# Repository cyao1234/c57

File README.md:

# c57

Low-cost bluetooth devboard with a ch572 MCU. To program it press the boot button, and use either mountriver studio or [ch32fun](https://github.com/cnlohr/ch32fun).

It is also very-low powered, and has on-board USB-C connector.

Features:
- Low-cost wch antenna
- On board antenna 
- Bootloader via USB
- Bare metal
- A lot of gpio
- on board usb c

This devboard lets you do low cost and low powered bluetooth communications. Best used with ch32fun

| Item | Price | Where |
| ---- | ----- | ----- |
| PCB + PCBA | $50 | JLC |

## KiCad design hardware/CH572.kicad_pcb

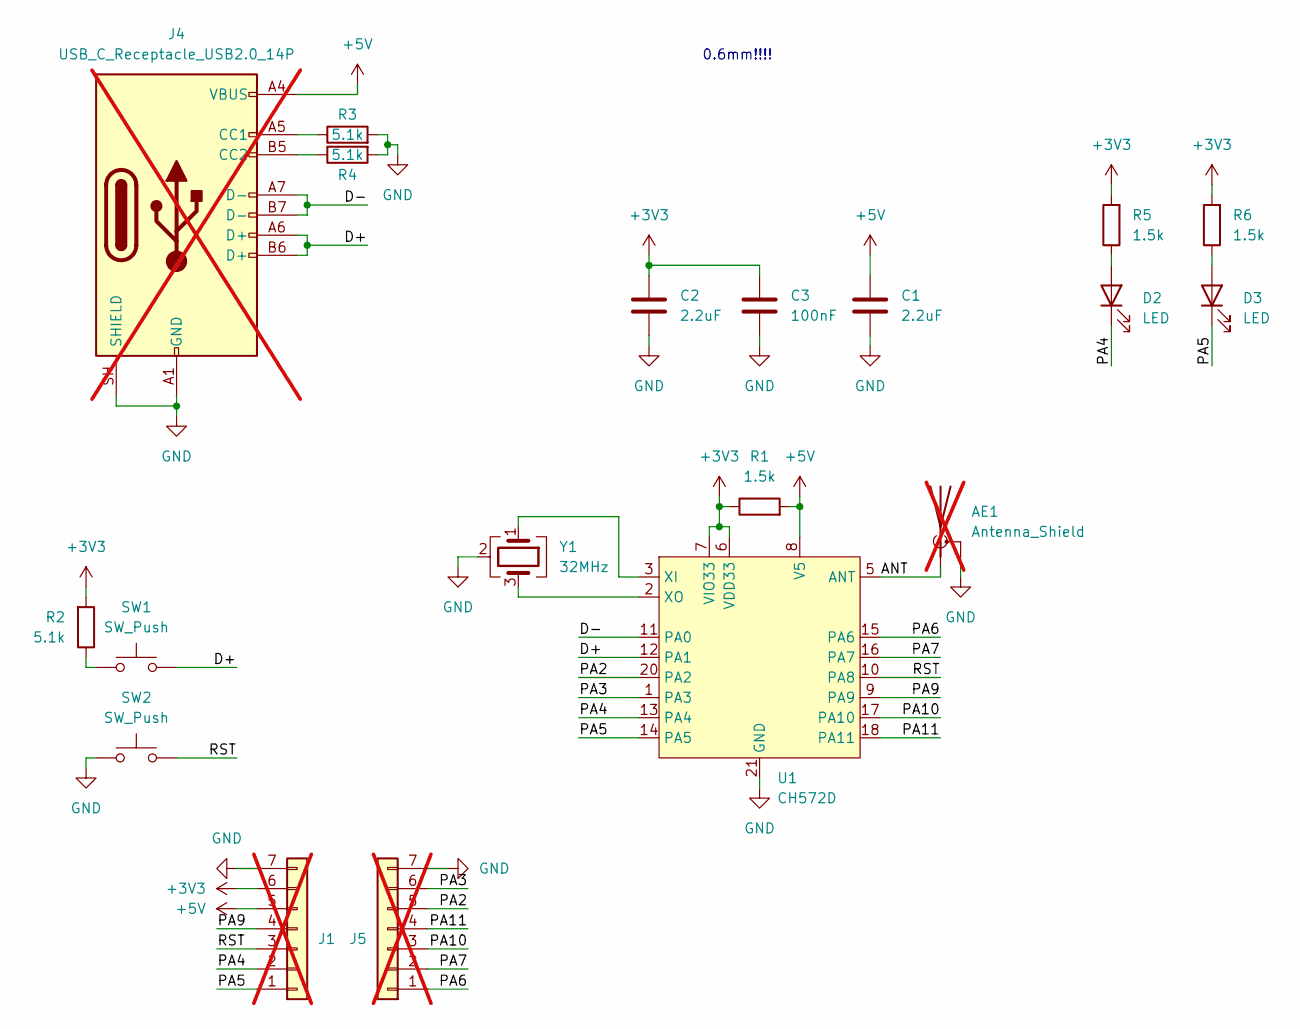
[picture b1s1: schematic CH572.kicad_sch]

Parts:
AE1: Antenna_Shield; WCH_CH572_2.4GHz; not fitted
C1, C2: 2.2uF; C_0402_1005Metric; LCSC Part # C159814
C3: 100nF; C_0402_1005Metric; LCSC Part # C466234
D2, D3: LED; LED_0402_1005Metric; LCSC Part # C965793
J1, J5: Conn_01x07; Castellated_1x07_P2.54mm_Vertical; not fitted
J4: USB_C_Receptacle_USB2.0_14P; USB_C_PADDLE; not fitted
R1, R5, R6: 1.5k; R_0402_1005Metric; LCSC Part # C25867
R2, R3, R4: 5.1k; R_0402_1005Metric; LCSC Part # C2906874
SW1, SW2: SW_Push; SW_Push_SPST_TSA016; LCSC Part # C2888428
U1: CH572D; UQFN-20-1EP_3x3mm_P0.4mm_EP1.85x1.85mm_ThermalVias; LCSC Part # C46597863
Y1: 32MHz; Crystal_SMD_2016-4Pin_2.0x1.6mm; LCSC Part # C2965584

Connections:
+3V3: C2.1, C3.1, J1.6, R1.1, R2.2, R5.2, R6.2, U1.6 (VDD33), U1.7 (VIO33)
+5V: C1.1, J1.5, J4.A4 (VBUS), J4.A9 (VBUS), J4.B4 (VBUS), J4.B9 (VBUS), R1.2, U1.8 (V5)
/ANT: AE1.1 (A), U1.5 (ANT)
/D+: J4.A6 (D+), J4.B6 (D+), SW1.2, U1.12 (PA1)
/D-: J4.A7 (D-), J4.B7 (D-), U1.11 (PA0)
/PA2: J5.5, U1.20 (PA2)
/PA3: J5.6, U1.1 (PA3)
/PA4: D2.1 (K), J1.2, U1.13 (PA4)
/PA5: D3.1 (K), J1.1, U1.14 (PA5)
/PA6: J5.1, U1.15 (PA6)
/PA7: J5.2, U1.16 (PA7)
/PA9: J1.4, U1.9 (PA9)
/PA10: J5.3, U1.17 (PA10)
/PA11: J5.4, U1.18 (PA11)
/RST: J1.3, SW2.2, U1.10 (PA8)
GND: AE1.2 (Shield), C1.2, C2.2, C3.2, J1.7, J4.A1 (GND), J4.A12 (GND), J4.B1 (GND), J4.B12 (GND), J4.SH (SHIELD), J5.7, R3.2, R4.2, SW2.1, U1.21 (GND), Y1.2 (G), Y1.4 (G)
unnamed: D2.2 (A), R5.1
unnamed: D3.2 (A), R6.1
unnamed: J4.A5 (CC1), R3.1
unnamed: J4.B5 (CC2), R4.1
unnamed: R2.1, SW1.1
unnamed: U1.3 (XI), Y1.1
unnamed: U1.2 (XO), Y1.3

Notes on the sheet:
0.6mm!!!!

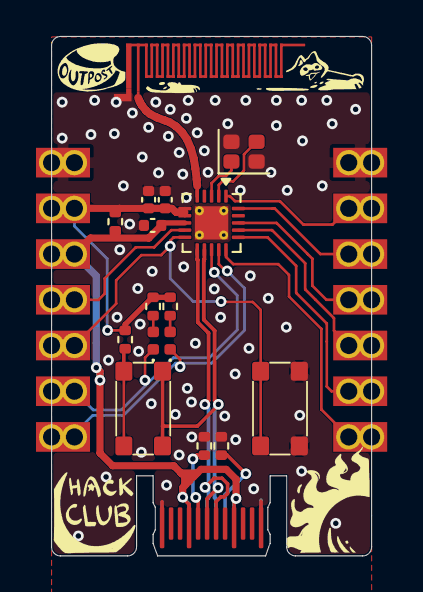
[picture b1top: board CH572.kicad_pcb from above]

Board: 2 copper layers, 17.8 x 28.9 mm, 19 parts (0 on the bottom side), 23 nets.

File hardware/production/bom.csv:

Designator,Footprint,Quantity,Value,LCSC Part #
"C1, C2",0402,2,2.2uF,C159814
C3,0402,1,100nF,C466234
"D2, D3",0402,2,LED,C965793
"R1, R5, R6",0402,3,1.5k,C25867
"R2, R3, R4",0402,3,5.1k,C2906874
"SW1, SW2",SW_Push_SPST_TSA016,2,SW_Push,C2888428
U1,UQFN-20-1EP_3x3mm_P0.4mm_EP1.85x1.85mm_ThermalVias,1,CH572D,C46597863
Y1,Crystal_SMD_2016-4Pin_2.0x1.6mm,1,32MHz,C2965584

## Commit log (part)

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2026-06-20 Init
